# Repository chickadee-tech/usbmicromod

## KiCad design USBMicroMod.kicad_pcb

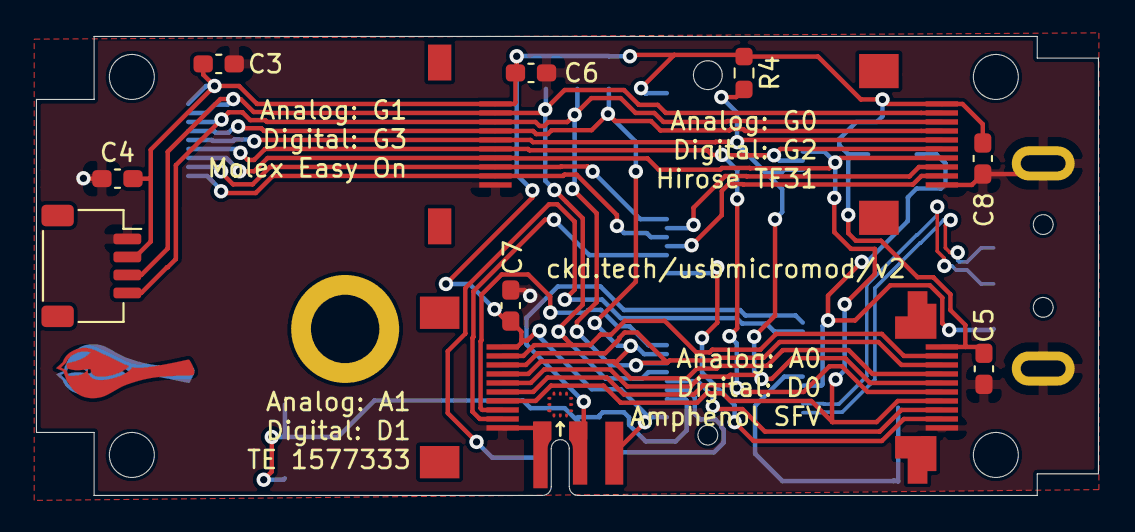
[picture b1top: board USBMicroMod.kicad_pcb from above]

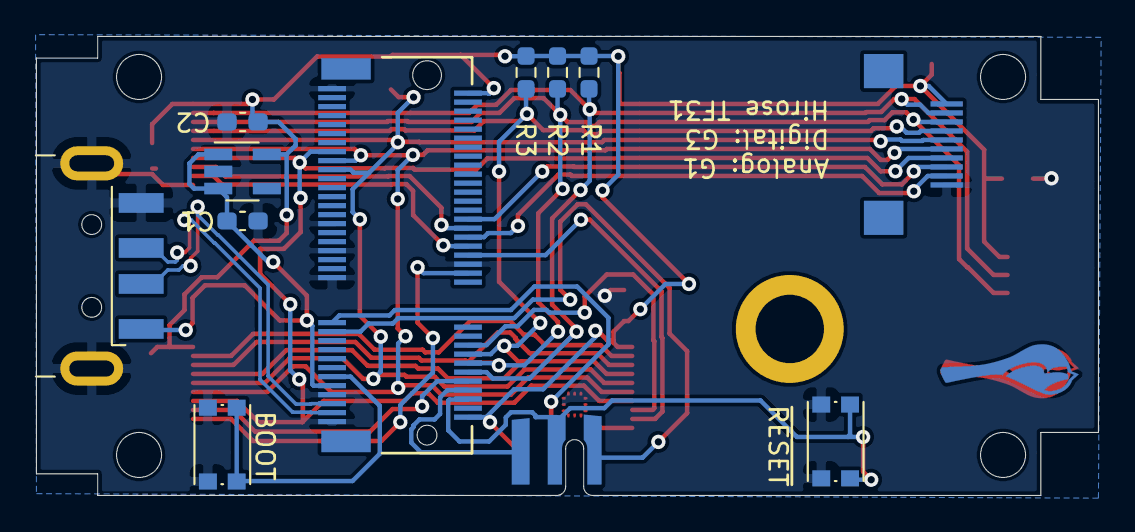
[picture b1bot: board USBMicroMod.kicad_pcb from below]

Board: 2 copper layers, 59.0 x 25.5 mm, 25 parts (12 on the bottom side), 24 nets.

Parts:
C1, C2, C3, C4, C5, C6, C7, C8: 1uF; C_0603_1608Metric_Pad1.08x0.95mm_HandSolder
H5: STAND-OFF-REFLOW2.5MM_TALL; STAND-OFF-REFLOW-M2.5
J1: MICROMOD-2222-C; MicroMod
J2: USB_A; USB_A_CNCTech_1001-011-01101_Horizontal
J3: DebugEdge_02x03; DebugEdge_2x03_Target
J4, J8: Conn_01x10; Hirose-TF31
J5: Conn_01x10; Amphenol-SFV
J6: Conn_01x10; Molex-Easy-On
J7: Conn_01x10; TE-1775333
J9: Conn_01x04_Male; JST_SH_SM04B-SRSS-TB_1x04-1MP_P1.00mm_Horizontal
R1, R2, R3: 2.2k; R_0603_1608Metric_Pad0.98x0.95mm_HandSolder
R4: 100k; R_0603_1608Metric_Pad0.98x0.95mm_HandSolder
SW1, SW2: SW_Push; SW_Push_1P1T_NO_CK_KMR2
U1: AP2112K-3.3; SOT-23-5_HandSoldering

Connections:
+3V3: C2.1, C3.1, C4.1, C5.1, C6.1, C7.1, C8.1, J1.2, J1.74, J3.5, J4.10, J5.10, J6.10, J7.10, J8.10, J9.2, R1.1, R2.1, R3.1, R4.1, U1.5
/A0: J1.34, J5.2
/A1: J1.38, J7.2
/A2: J1.40, J4.2
/A3: J1.42, J6.2, J8.2
/D0: J1.10, J5.3
/D1: J1.18, J7.3
/D2: J1.44, J4.3
/D3: J1.46, J6.3, J8.3
/INT: J1.16, J4.7, J5.7, J6.7, J7.7, J8.7, R3.2
/MISO: J1.61, J4.4, J5.4, J6.4, J7.4, J8.4
/MOSI: J1.59, J4.5, J5.5, J6.5, J7.5, J8.5
/SCK: J1.57, J4.6, J5.6, J6.6, J7.6, J8.6, R4.2
/SCL: J1.14, J4.8, J5.8, J6.8, J7.8, J8.8, J9.4, R2.2
/SDA: J1.12, J4.9, J5.9, J6.9, J7.9, J8.9, J9.3, R1.2
/SWCLK: J1.21, J3.3
/SWDIO: J1.23, J3.2
/SWO: J1.8, J3.6
/USB_D+: J1.3, J2.3
/USB_D-: J1.5, J2.2
/~BOOT: J1.11, SW2.1
/~RESET: J1.6, J3.4, SW1.1
GND: C1.2, C2.2, C3.2, C4.2, C5.2, C6.2, C7.2, C8.2, J1.1, J1.7, J1.33, J1.36, J1.39, J1.45, J1.75, J2.4, J2.5, J3.1, J4.1, J5.1, J6.1, J7.1, J8.1, J9.1, SW1.2, SW2.2, U1.2
VBUS: C1.1, J1.9, J2.1, U1.1, U1.3

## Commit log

2021-02-10 usb micromod dongle
2021-02-14 Final v1
2021-03-10 Move USB and one 10pin
